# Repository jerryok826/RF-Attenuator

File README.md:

# RF Attenuator

## Project Description
I always liked the HP/Agilent 355 Step Attenuators. Now with Kicad and low cost PCB fabrication I thought I should just design my own. The attenuator uses BNC connector rather than SMA beause I like the quick disconnet feature. The design is base on 1 watt resistors so that the power limit. Total Attenuation is 62DB in 1 DB steps.

### Project Status
The project is complete and has be verifyed with a Rigol DSA816 spectrum analyer from 1MHz to 30MHz.

## Design Files
### Electrical Design Files
This project was designed with Kicad 7.X

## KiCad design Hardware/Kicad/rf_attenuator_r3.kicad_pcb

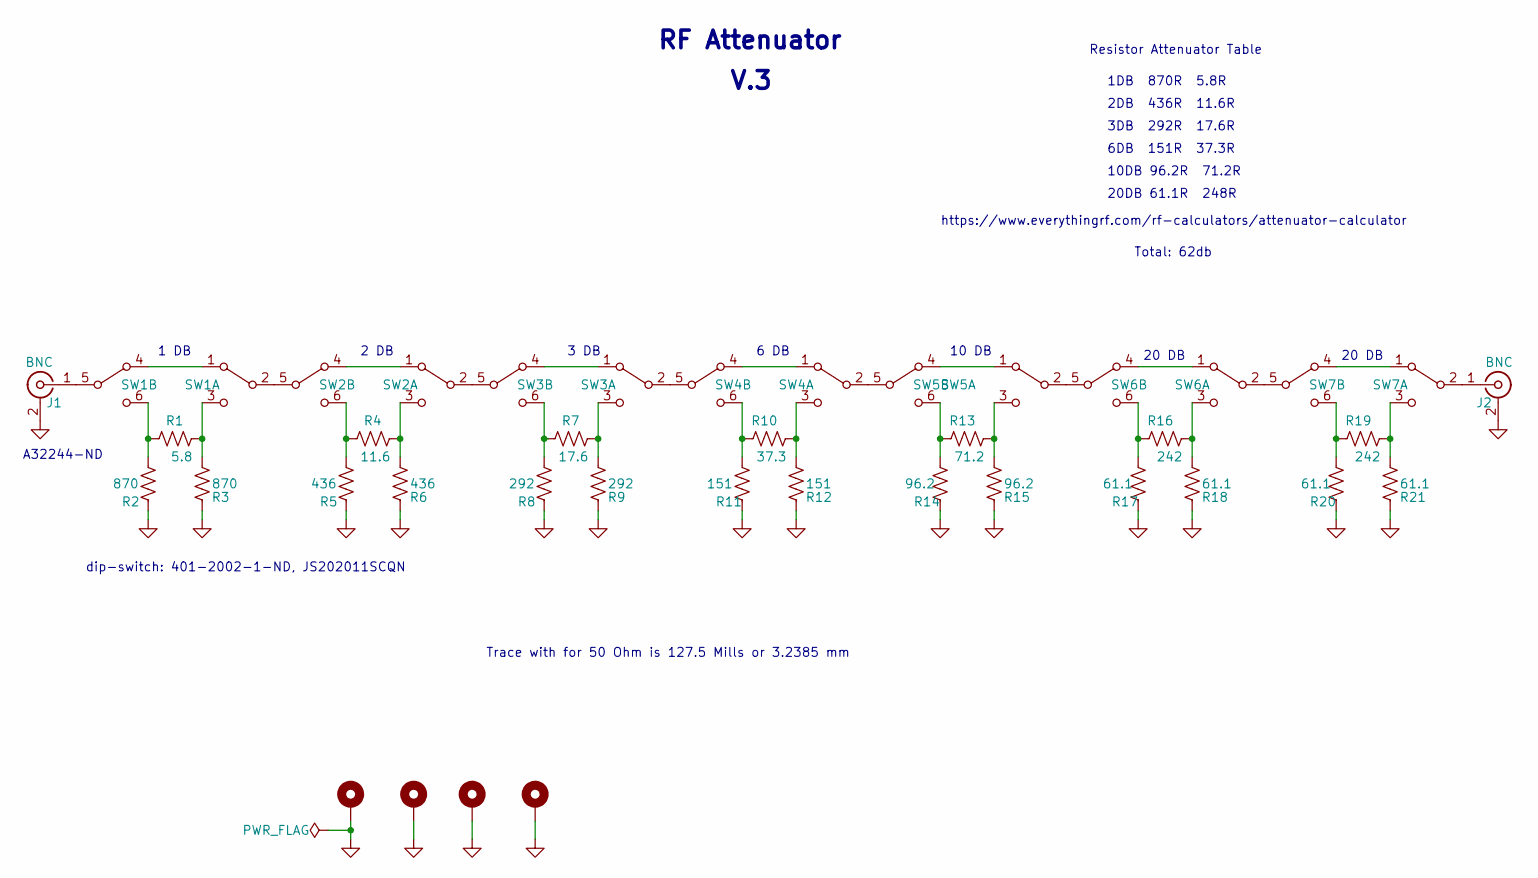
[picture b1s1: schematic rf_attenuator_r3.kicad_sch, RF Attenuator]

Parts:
H1, H2, H3, H4: MountingHole_Pad; MountingHole_3.2mm_M3_ISO7380_Pad_TopBottom
J1, J2: BNC; BNC_Amphenol_B6252HB-NPP3G-50_Horizontal
R1: 5.8; R_2512_6332Metric_Pad1.40x3.35mm_HandSolder
R2, R3: 870; R_2512_6332Metric_Pad1.40x3.35mm_HandSolder
R4: 11.6; R_2512_6332Metric_Pad1.40x3.35mm_HandSolder
R5, R6: 436; R_2512_6332Metric_Pad1.40x3.35mm_HandSolder
R7: 17.6; R_2512_6332Metric_Pad1.40x3.35mm_HandSolder
R8, R9: 292; R_2512_6332Metric_Pad1.40x3.35mm_HandSolder
R10: 37.3; R_2512_6332Metric_Pad1.40x3.35mm_HandSolder
R11, R12: 151; R_2512_6332Metric_Pad1.40x3.35mm_HandSolder
R13: 71.2; R_2512_6332Metric_Pad1.40x3.35mm_HandSolder
R14, R15: 96.2; R_2512_6332Metric_Pad1.40x3.35mm_HandSolder
R16, R19: 242; R_2512_6332Metric_Pad1.40x3.35mm_HandSolder
R17, R18, R20, R21: 61.1; R_2512_6332Metric_Pad1.40x3.35mm_HandSolder
SW1, SW2, SW3, SW4, SW5, SW6, SW7: SW_DPDT_x2; SW_DPDT_CK_JS202011JCQN

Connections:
GND: H1.1, H2.1, H3.1, H4.1, J1.2 (Ext), J2.2 (Ext), R2.2, R3.2, R5.2, R6.2, R8.2, R9.2, R11.2, R12.2, R14.2, R15.2, R17.2, R18.2, R20.2, R21.2
unnamed: J1.1 (In), SW1.5 (B)
unnamed: J2.1 (In), SW7.2 (B)
unnamed: SW1.1 (A), SW1.4 (A)
unnamed: SW1.2 (B), SW2.5 (B)
unnamed: R1.2, R3.1, SW1.3 (C)
unnamed: R1.1, R2.1, SW1.6 (C)
unnamed: SW2.1 (A), SW2.4 (A)
unnamed: SW2.2 (B), SW3.5 (B)
unnamed: R4.2, R6.1, SW2.3 (C)
unnamed: R4.1, R5.1, SW2.6 (C)
unnamed: SW3.1 (A), SW3.4 (A)
unnamed: SW3.2 (B), SW4.5 (B)
unnamed: R7.2, R9.1, SW3.3 (C)
unnamed: R7.1, R8.1, SW3.6 (C)
unnamed: SW4.1 (A), SW4.4 (A)
unnamed: SW4.2 (B), SW5.5 (B)
unnamed: R10.2, R12.1, SW4.3 (C)
unnamed: R10.1, R11.1, SW4.6 (C)
unnamed: SW5.1 (A), SW5.4 (A)
unnamed: SW5.2 (B), SW6.5 (B)
unnamed: R13.2, R15.1, SW5.3 (C)
unnamed: R13.1, R14.1, SW5.6 (C)
unnamed: SW6.1 (A), SW6.4 (A)
unnamed: SW6.2 (B), SW7.5 (B)
unnamed: R16.2, R18.1, SW6.3 (C)
unnamed: R16.1, R17.1, SW6.6 (C)
unnamed: SW7.1 (A), SW7.4 (A)
unnamed: R19.2, R21.1, SW7.3 (C)
unnamed: R19.1, R20.1, SW7.6 (C)

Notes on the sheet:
6 DB
dip-switch: 401-2002-1-ND, JS202011SCQN
3DB 292R 17.6R
10DB 96.2R 71.2R
V.3
2 DB
https://www.everythingrf.com/rf-calculators/attenuator-calculator
RF Attenuator
6DB 151R 37.3R
Trace with for 50 Ohm is 127.5 Mills or 3.2385 mm
20 DB
20DB 61.1R 248R
10 DB
A32244-ND
Total: 62db
1 DB
1DB 870R 5.8R
Resistor Attenuator Table
2DB 436R 11.6R
3 DB

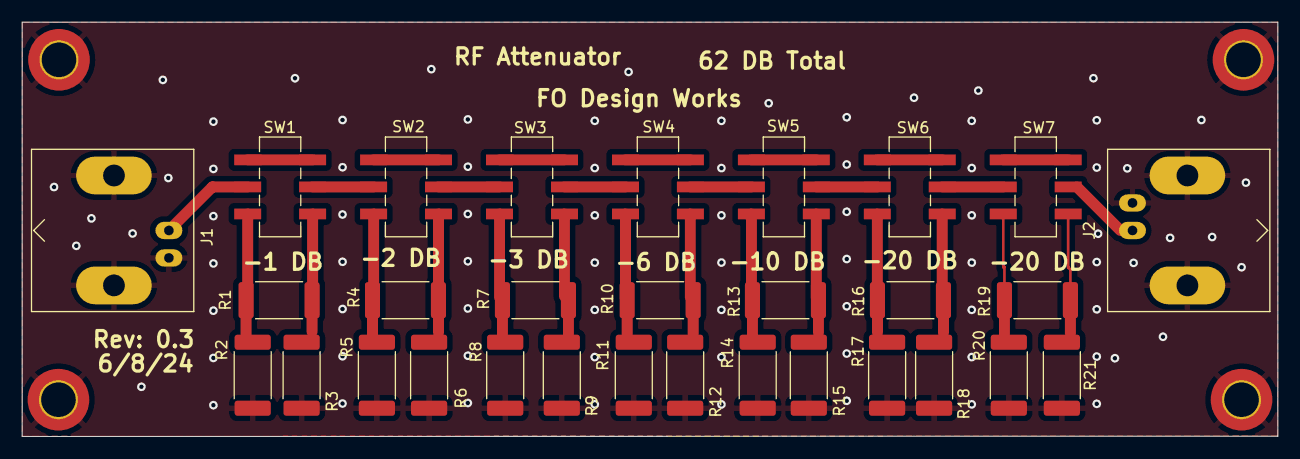
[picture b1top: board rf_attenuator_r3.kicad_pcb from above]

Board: 2 copper layers, 116.1 x 38.3 mm, 34 parts (0 on the bottom side), 30 nets.
